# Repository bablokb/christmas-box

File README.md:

A Christmas-box with sound and display
======================================

This project is about a Christmas-box, that plays a song and
displays images when the lid is opened:

Electronics
-----------

The basis for the electronics is a Raspberry Pi Pico, together
with a small 1.8"-TFT-display and a PAM802A amplifier. The TFT
and the speaker are in the lid, whereas the Pico is inside of
the box.

(The PAM802A is below the green support PCB).

Software
--------

The Pico runs a small CircuitPython-script that has everything
necessary to display files and to play MP3. The source-code
is in `src/`, some sample media-files are in `src/media/`.

Images must be in BMP-format and the MP3-files are downsampled,
because the Pico does not have enough power to play files with
higher sample-rate.

Build
-----

The box itself was designed using OpenSCAD (source-code in `3D/`).
There is an outer-shell and a smaller inner-shell to make room
for the battery and the Pico:

The lid consists also of two parts:
the outer-part and a frame for the TFT and the speaker.

More images are in the `build/`-directory.

OpenSCAD allows parameters for all dimensions, so you can adjust
the sizes of the parts to your needs without any problems.
Note that I print with tight tolerances, depending on your printer,
you must change this.

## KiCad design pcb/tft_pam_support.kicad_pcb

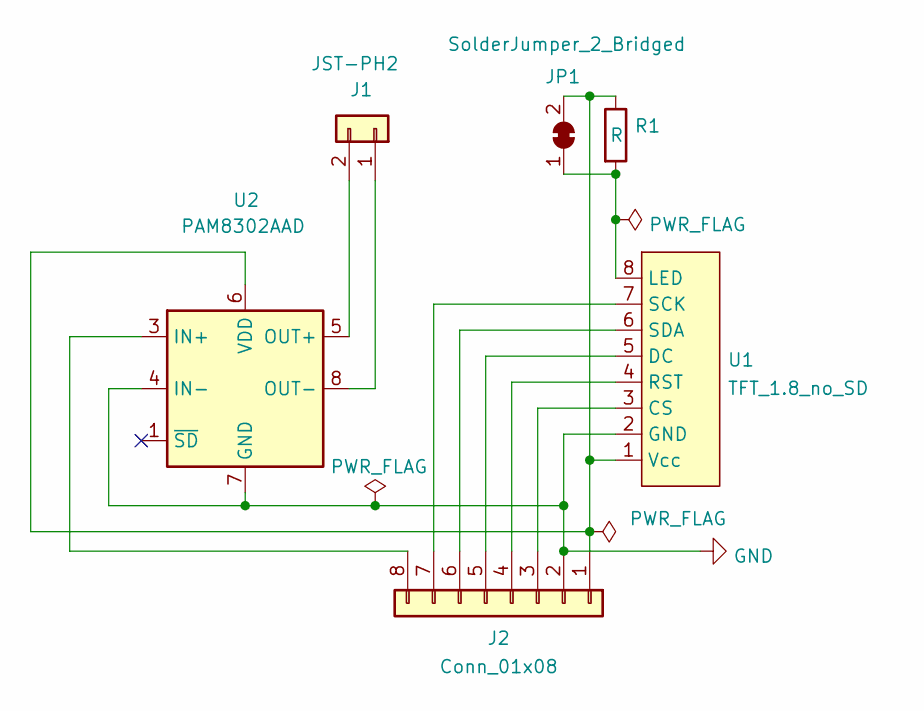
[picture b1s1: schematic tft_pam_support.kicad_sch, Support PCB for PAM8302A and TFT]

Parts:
J1: JST-PH2; JST_PH_S2B-PH-SM4-TB_1x02-1MP_P2.00mm_Horizontal
J2: Conn_01x08; PinHeader_1x08_P2.54mm_Horizontal
JP1: SolderJumper_2_Bridged; SolderJumper-2_P1.3mm_Bridged_RoundedPad1.0x1.5mm
R1: R; R_1206_3216Metric_Pad1.30x1.75mm_HandSolder
U1: TFT_1.8_no_SD
U2: PAM8302AAD; PAM8302A_Breakout

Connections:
GND: J2.2, U1.2 (GND), U2.4 (IN-), U2.7 (GND)
unnamed: J1.1, U2.8 (OUT-)
unnamed: J1.2, U2.5 (OUT+)
unnamed: J2.1, JP1.2 (B), R1.1, U1.1 (Vcc), U2.6 (VDD)
unnamed: J2.3, U1.3 (CS)
unnamed: J2.4, U1.4 (RST)
unnamed: J2.5, U1.5 (DC)
unnamed: J2.6, U1.6 (SDA)
unnamed: J2.7, U1.7 (SCK)
unnamed: J2.8, U2.3 (IN+)
unnamed: JP1.1 (A), R1.2, U1.8 (LED)

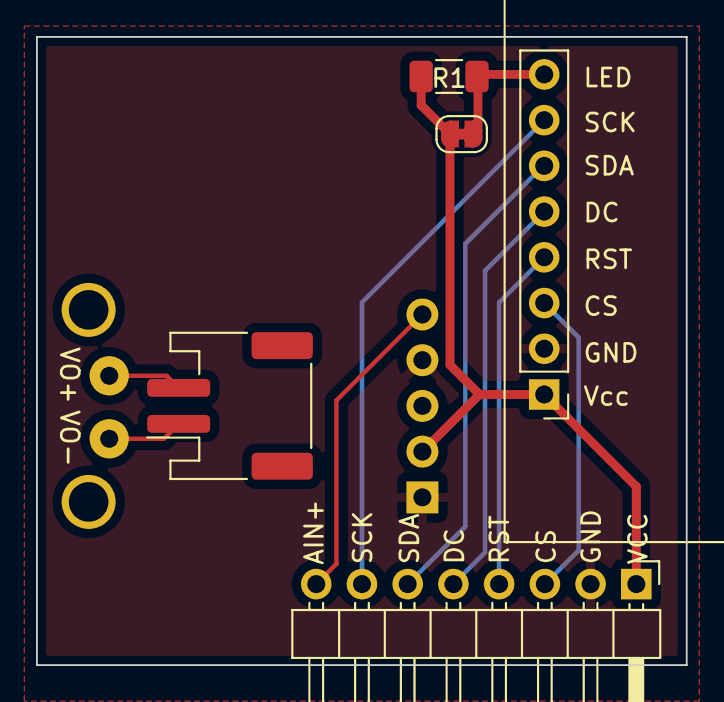
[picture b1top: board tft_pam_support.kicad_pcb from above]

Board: 2 copper layers, 36.1 x 34.9 mm, 6 parts (1 on the bottom side), 11 nets.

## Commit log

2022-07-28 added fp-info-cache
2022-07-28 added *.zip and jlcpcb/
2022-07-28 replaced footprint for JST-connector THT->SMD
2022-08-04 redefined pins for simplified cabling
2022-08-05 added *.sch-bak
2022-08-05 refactored bat-holder dimensions to dimensions.scad
2022-08-05 renamed h_top to z_top
2022-08-08 create top-size frame
2022-08-08 refactored dimension-constants to dimensions.scad
2022-08-14 added dimensions for inner-shell
2022-08-18 added dimensions for inner-plate
2022-08-22 bugfix: interrupt image-playback after end of sound-file
2022-09-06 add thickness
2022-09-07 fix defs for hinges
2022-09-07 fix y-dimension of hinges
2022-10-20 added content
2023-02-25 fixed size
